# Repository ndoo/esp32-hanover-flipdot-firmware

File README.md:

# ESP32 Hanover Flip-dot Sign Controller

## PCB

Reference PCB is available at [ndoo/esp32-hanover-flipdot](https://github.com/ndoo/esp32-hanover-flipdot)

## Demo Video

[ESP32 Hanover Flip-dot Sign Controller - Demos](https://youtu.be/oSv1yEUelBg)

## Firmware

### IDE Prerequisites

You will need a working [VS Code](https://code.visualstudio.com/) and [PlatformIO](https://platformio.org/) development environment, with ESP32 support installed.

Libraries should automatically download as they have been specified in `platformio.ini`.

### First Use

#### Powering the Board

A freshly assembled board will not have any sketch running on it, and will be in bootloader bode waiting for firmware upload over serial. You will need a TTL USB-serial adapter, and one of the following methods of powering the board:

* Connect Tx, Rx, VCC and GND to USB-serial adapter - **USB-serial adapter must be set to 3.3V VCC or the ESP32 SIP will be irreversibly damaged**
* Connect Tx, Rx and GND to USB-serial adapter, then connect 18VDC power supply - **ground PCB to USB-serial adapter before connecting DC supply to avoid ESD**

**Do not connect RS-232 level signalling to the board, the ESP32 SIP will be damaged by signalling above TTL levels.**

#### Compiling and Uploading Sketch

The default `platformio.ini` provided here is configured to OTA upload for your convenience, however that means you need to edit this file for the initial flash, in order to program over USB-serial, as the board is not running firmware capable of OTA updates.

Comment these 2 lines out by preceding them with a semicolon (`;`):

```
upload_protocol = espota
upload_port = Hanover-Flipdot.local
```

Then, test the build by clicking the tick in the lower left status bar of VS Code + PlatformIO.

If the build succeeds, click the rightwards-pointing arrow in the lower left status bar of VS Code + PlatformIO. This will link the firmware and attempt to upload it to the board's ESP32 over USB-serial.

#### Configuring Wi-Fi

You should see a new wireless AP with the SSID `ESP_<YOUR_ESP_UNIQUE_MAC>`. Connect to it and you should be automatically redirected to a portal that allows you to connect the ESP32 to your Wi-Fi.

If the connection is successful, you should be able to send data to the board using the Python scripts found in the `demos` folder. If the connection fails, the ESP32 will automatically time out and re-start the temporary wireless AP for you to continue Wi-Fi setup.

Don't forget to uncomment the previously commented-out lines in `platformio.ini` to re-enable OTA uploads.

#### Rescue Programming

If you need to re-upload a sketch over serial, take note that this board does not have automatic boot and reset circuitry, so you will need to press the two buttons on the board in the following sequence to enter download mode, before uploading a sketch:

1. Hold down RST button
2. Hold down PGM button
3. Release RST button
4. Release PGM button

This may take a few tries to get the timing right, as the buttons are tiny and placed close together.

#### Troubleshooting

* Board not receiving UDP packets
  * The board, by default, listends on multicast IP 239.1.2.3 on UDP port 8080 (port can be changed in `include/main.h`)
  * Your LAN routers, switches or Wi-Fi access points may be configured to drop multicast packets, or may need IGMP snooping to be enabled
* OTA not working on Windows due to Hanover-Flipdot.local not resolving
  * You may need to install an mDNS resolver software such as [Apple's Bonjour Print Services for Windows](https://support.apple.com/kb/DL999)

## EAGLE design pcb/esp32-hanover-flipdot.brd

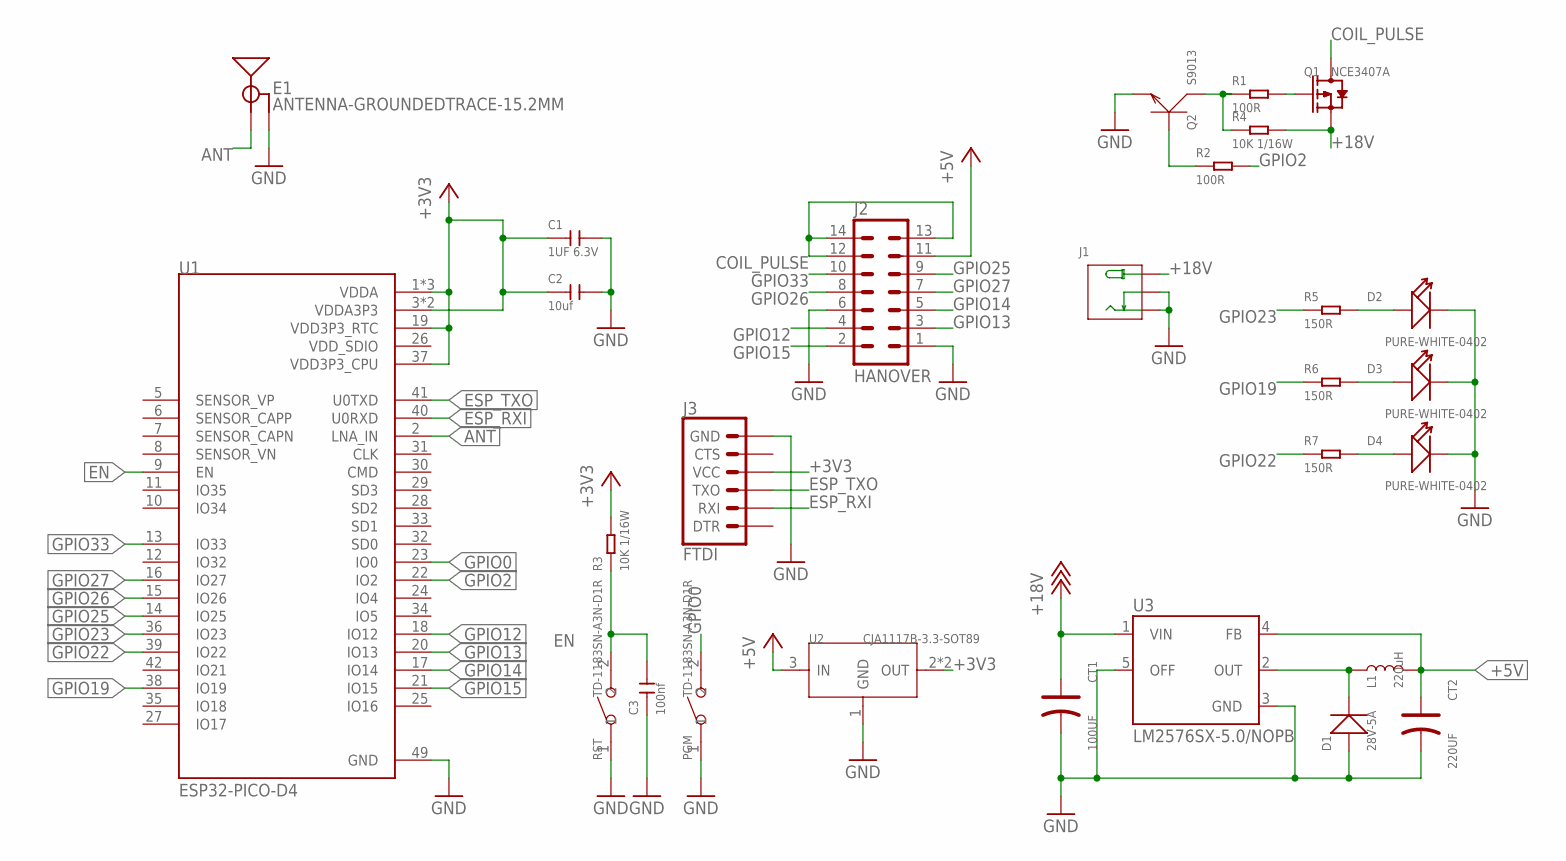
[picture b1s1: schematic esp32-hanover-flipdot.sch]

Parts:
C1: 1UF 6.3V; C0402
C2: 10uf; C0402
C3: 100nf; C0402
CT1: 100UF; ELECTRO-SMD-C-6MM; MPN 302030000
CT2: 220UF; ELECTRO-SMD-C-6MM
D1: 28V-5A; DO-214AA
D2, D3, D4: PURE-WHITE-0402; LED-0402
E1: ANTENNA-GROUNDEDTRACE-15.2MM; TRACE_ANTENNA_2.4GHZ_15.2MM
J1: DC-005; 3P-L14.2*W11.0*H9.0MM
J2: HANOVER; ML14
J3: FTDI; 6_PIN_SERIAL_TARGET_SIDE_W_SILK
L1: 220uH; CR54
PGM: TD-1183SN-A3N-D1R; SW2-2.6-3.0X2.5X1.2+0.4MM
Q1: NCE3407A; SOT-23
Q2: S9013; SOT-23
R1, R2: 100R; R0402
R3, R4: 10K 1/16W; R0402
R5, R6, R7: 150R; R0402; MPN RC0402FR-07150RL
RST: TD-1183SN-A3N-D1R; SW2-2.6-3.0X2.5X1.2+0.4MM
U1: ESP32-PICO-D4; PQFN50P700X700X104-49N
U2: CJA1117B-3.3-SOT89; SOT-89
U3: LM2576SX-5.0/NOPB; TO263-5

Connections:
+3V3: C1.1, C2.1, J3.P$4 (VCC), R3.2, U1.1 (VDDA), U1.3 (VDDA3P3), U1.4 (VDDA3P3), U1.19 (VDD3P3_RTC), U1.37 (VDD3P3_CPU), U1.43 (VDDA), U1.46 (VDDA), U2.2 (OUT), U2.4 (OUT)
+5V: CT2.+, J2.11, L1.P$2 (2), U2.3 (IN), U3.4 (FB)
+18V: CT1.+, J1.+B (+), J1.+T (+), Q1.2 (S), R4.2, U3.1 (VIN)
ANT: E1.ANT (SIGNAL), U1.2 (LNA_IN)
COIL_PULSE: J2.12, J2.13, J2.14, Q1.3 (D)
EN: C3.2, R3.1, RST.2, U1.9 (EN)
ESP_RXI: J3.P$3 (RXI), U1.40 (U0RXD)
ESP_TXO: J3.P$2 (TXO), U1.41 (U0TXD)
GND: C1.2, C2.2, C3.1, CT1.-, CT2.-, D1.+, D2.-, D3.-, D4.-, E1.GND, J1.-1B (-), J1.-1T (-), J1.-2B (CDN), J1.-2T (CDN), J2.1, J2.6, J3.P$6 (GND), PGM.1, Q2.2 (E), RST.1, U1.49 (GND), U2.1 (GND), U3.3 (GND), U3.5 (OFF)
GPIO0: PGM.2, U1.23 (IO0)
GPIO2: R2.2, U1.22 (IO2)
GPIO12: J2.4, U1.18 (IO12)
GPIO13: J2.3, U1.20 (IO13)
GPIO14: J2.5, U1.17 (IO14)
GPIO15: J2.2, U1.21 (IO15)
GPIO19: R6.1, U1.38 (IO19)
GPIO22: R7.1, U1.39 (IO22)
GPIO23: R5.1, U1.36 (IO23)
GPIO25: J2.9, U1.14 (IO25)
GPIO26: J2.8, U1.15 (IO26)
GPIO27: J2.7, U1.16 (IO27)
GPIO33: J2.10, U1.13 (IO33)
unnamed: Q1.1 (G), R1.2
unnamed: Q2.3 (C), R1.1, R4.1
unnamed: Q2.1 (B), R2.1
unnamed: D1.-, L1.P$1 (1), U3.2 (OUT)
unnamed: D2.+, R5.2
unnamed: D3.+, R6.2
unnamed: D4.+, R7.2
VDD_SDIO: U1.26 (VDD_SDIO)

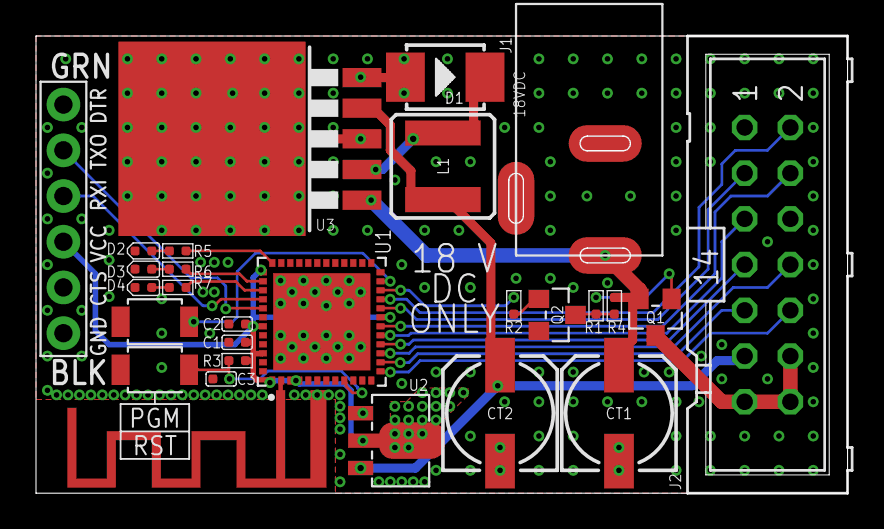
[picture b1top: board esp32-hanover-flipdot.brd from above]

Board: 2 copper layers, 45.1 x 25.4 mm, 28 parts (0 on the bottom side), 29 nets.

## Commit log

2018-11-21 Changed more tName silkscreen text to 11% ratio, fixed R2 silkscreen overlap with CT2 pad, update PCB image.
2020-05-04 Add PlatformIO project for code that drives the board
    Add PlatformIO project for code that drives the board. Documentation TODO.
2020-05-04 Fix reset routines and transmit data over binary UDP
2020-05-05 Move demo from OpenCV + PIL to OpenCV-only, abstract into library for future demos
2020-05-05 imageToBinary optimizations
2020-05-05 Add clock demo
2020-05-05 PCB: Disconnect dot board pin 13, 14. Add 18VDC and warning text. Increase space around J2.
    Disconnect dot-board pin 13 and 14 from 18VDC, seems to cause overheating of dot 0,0 on dot boards when boards are not enabled. Works fine without anyway - tested by cutting ribbon cable pins 13, 14.
    Added 18VDC only warning text. Add warning text to disconnect power before connecting or disconnecting dot boards.
    Increase space around J2 as the connector housing is causing stress to neighboring components.
2020-05-05 Fix Eagle Seeedstudio DRC
    Routed missing airwires and approved clearance issues
2020-05-05 Update README with first use programming instructions
2020-05-05 Create esp32-hanover-flipdot_2020-05-05-seeed-fusion.zip
    Generate Seeed Fusion PCB Gerbers using Eagle's built in Seeed Fusion 2-layer template
2020-05-05 Update README.md
    Recommend buying 2.54mm through-holes locally to save time/money
2020-05-05 Fix warning silkscreen clipping outside of board dimension
2020-05-06 More Demos and Updates to Demos
    New demos:
    * clock.py - A simple clock
    * fill.py - Dotboard test - cycles between all on and all off
    * webcam.py - Sends webcam feed to dotboard (written for Windows, trivial to adapt by changing the capture device to 0)
    Improvements/changes
    * imageToBinary.py - invert image as contrast tends to favor white on black on flipdots
2020-05-06 Firmware: Improve stability for 3+ dot boards
    Improvements for stability for 3 dot boards (and presumably the maximum supported, 4) by adding additional exponential delay for each dot board chained from the first.
    The main difference is that voltage droops due to the longer distance (resistance/capacitance) requires extra coil pulse time.
    Disable Wi-Fi sleep again, as heat output is manageable; I had faulty dot boards drawing heavily on the 5V rail causing the main switching regulator to generate excessive heat, but it turns out the E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
    Disable display from UDP during OTA update to avoid blocking OTA thread.
2020-05-06 PCB: Layout improvements and parts substitutions
    Board:
    * Increase ground plane stitching especially for heatsinking of regulators and ESP32
    * Add pour and stitching on +3V3 LDO regulator for heatsinking
    * Increase voltage trace sizes to conduct heat away from power components/decrease voltage droop
    Schematic:
    * Disconnect dot board pin 14 from 18V, it seems to cause erratic behavior on dot boards. Not sure what the function of this 18V supply pin is, but boards work fine with this line snipped off
2020-05-06 PCB: Cleanup for Seeed Fusion
    Board and Schematic:
    * Change LM2576 part to match BOM
    Other documents:
    * Exported a new set of Gerbers and matching pick and place files and top of PCB drawing
2020-05-06 Update clock.py
    Needed color inversion in the clock drawing routine, since imageToBinary now does an inversion
2020-05-07 Update Hanover_Flipdot.h
    Add support for older revision of PCB
2020-05-07 Update bom.csv
    J2 should be vertical header and not right angle
2020-05-07 Hanover_Flipdot: Remove support for vertically stacked dot boards; Change buffer to 1D array of 32-bit columns
    Remove support for vertically stacked dot boards:
    Now dot boards can only be chained left to right, there is no support for vertically stacked dotboards e.g. 1x2, 2x2 dotboards. In any case, 2D dotboard matrixes was never really supported by the wri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
    Change buffer to 1D array of 32-bit columns:
    This is to make the buffer format much more similar to Hanover's RS-485 signalling, in preparating for future work to integrate Hanover RS-485 protocol support.
    Other functions had to be re-written to become bitwise operations to the buffer.
    UDP receive of video frames now
2020-05-07 Demos: Size updated to 128x32, imageToBinary adapted for new buffer format
    Size updated to 128x32 to match a real Hanover EDS
    imageToBinary adapted for new buffer format, which requires rotation and flip to put pixels in the correct Hanover protocol compatible order (colums -> rows)
2020-05-07 Demos: Add image.py
    Sends an image to the dot board. This inverts twice (i.e. it does not invert), so your image should be color on black for best contrast.
2020-05-07 Firmware: Improve error messages
    Error messages now backup previous contents, and restore the original contents.
    The most noticeable improvement is that Wi-Fi disconnects no longer cause board contents to be lost.
2020-05-08 Demos: Clock visual changes, font filename case sensitive
    Clock visual layout changes
    Fix font file name for case sensitive filesystems.
2020-05-08 Clock: Update fonts and layout, update font licenses
2020-05-08 Firmware: Fix coil pulse uint8_t overflow, change enable/disable routine, LED pin naming changes, increase coil pulse times
    Fix coil pulse uint8_t overflow:
    flipDot() routine used uint8_t type for pulse_time, leading to an integer overflow that prevented further dot boards from flipping dots due to insufficient pulse_time. uint16_t data type fixes this (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
    Change enable/disable routine:
    A previous change to enable-only routine in commit 3168280bb8c06442f1713e7cbb857c4e17712baf causes dot board 4 to be left enabled after a writeDisplay(), it should be left disabled when not in use; r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
    LED pin naming changes for clarity.
    Increase coil
2020-05-12 pcb: Connect dot board pin 14 to COIL_PULSE (pin 12, pin 13) too
    The 18V supply on this pin doesn't seem to be used, as it's wired to column darlington arrays while the dot boards seem to use the row darlingtons to source/sink. In any case, it should be safe to co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
2020-05-12 pcb: Increase isolation and ground stitching around 18V pulse line
2020-05-17 Clean up non-firmware files for fork to firmware-only repository
2020-08-24 Add gameoflife demo and change some board sizes to 64*32 for testing

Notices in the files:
parts and their libraries:
SparkFun-RF: Licensing: Creative Commons ShareAlike 4.0 International - https://creativecommons.org/licenses/by-sa/4.0
